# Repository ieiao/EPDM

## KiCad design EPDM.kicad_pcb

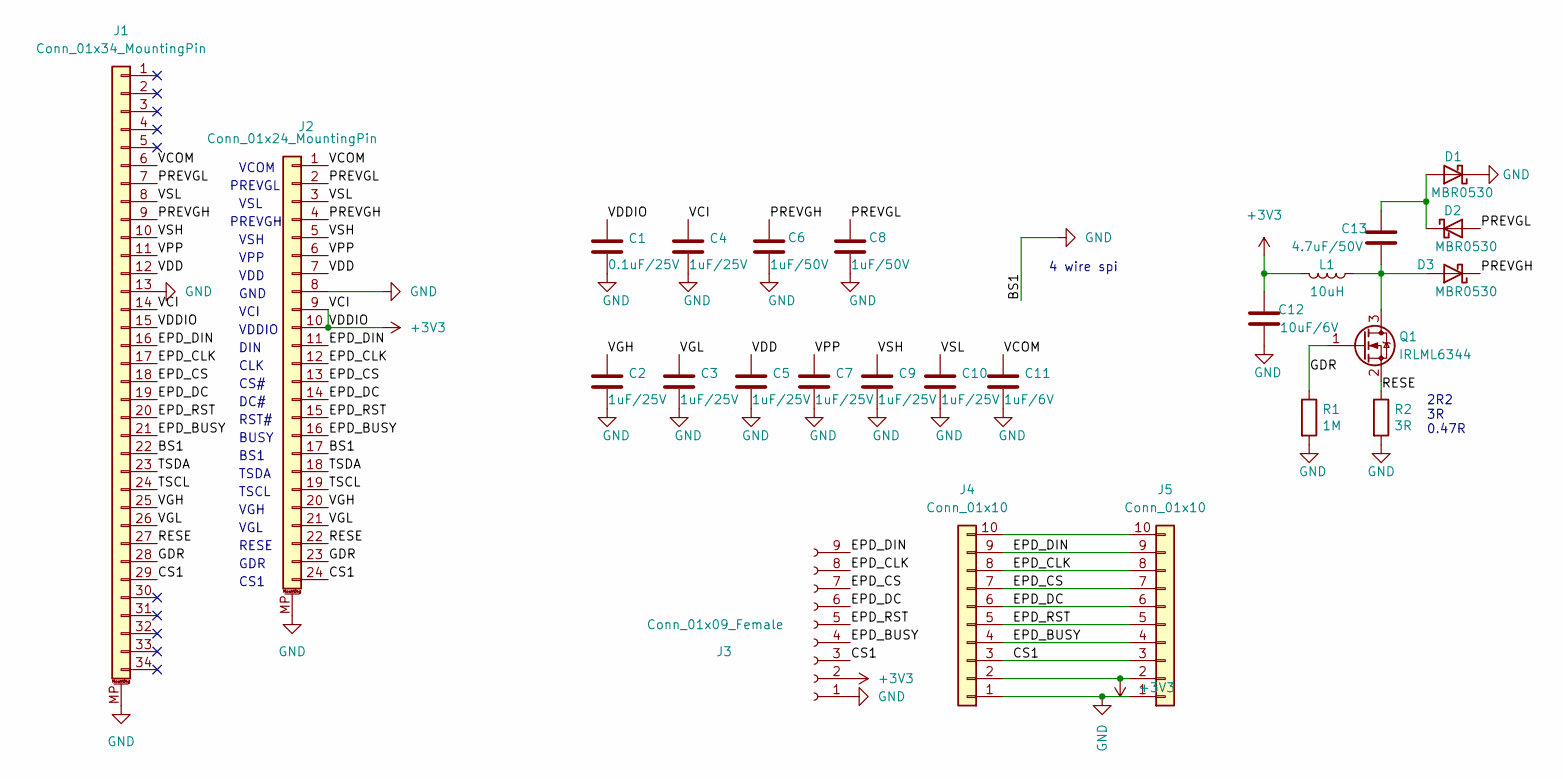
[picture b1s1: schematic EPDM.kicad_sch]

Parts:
C1: 0.1uF/25V; C_0603_1608Metric
C2, C3, C4, C5, C7, C9, C10: 1uF/25V; C_0603_1608Metric
C6, C8: 1uF/50V; C_0603_1608Metric
C11: 1uF/6V; C_0603_1608Metric
C12: 10uF/6V; C_0805_2012Metric
C13: 4.7uF/50V; C_0805_2012Metric
D1, D2, D3: MBR0530; D_SOD-123
J1: Conn_01x34_MountingPin; TE_3-1734839-4_1x34-1MP_P0.5mm_Horizontal
J2: Conn_01x24_MountingPin; TE_2-1734839-4_1x24-1MP_P0.5mm_Horizontal
J3: Conn_01x09_Female; PinHeader_1x09_P1.27mm_Vertical
J4: Conn_01x10; PinHeader_1x10_P1.27mm_Vertical
J5: Conn_01x10; PinHeader_1x10_P2.54mm_Vertical
L1: 10uH; L_Coilcraft_XxL4020
Q1: IRLML6344; SOT-23
R1: 1M; R_0603_1608Metric
R2: 3R; R_0603_1608Metric

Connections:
+3V3: C1.1, C4.1, C12.2, J1.14, J1.15, J2.9, J2.10, J3.2, J4.2, J5.2, L1.2
/CS1: J1.29, J2.24, J3.3, J4.3, J5.3
/EPD_BUSY: J1.21, J2.16, J3.4, J4.4, J5.4
/EPD_CLK: J1.17, J2.12, J3.8, J4.8, J5.8
/EPD_CS: J1.18, J2.13, J3.7, J4.7, J5.7
/EPD_DC: J1.19, J2.14, J3.6, J4.6, J5.6
/EPD_DIN: J1.16, J2.11, J3.9, J4.9, J5.9
/EPD_RST: J1.20, J2.15, J3.5, J4.5, J5.5
/GDR: J1.28, J2.23, Q1.1 (G), R1.1
/PREVGH: C6.1, D3.1 (K), J1.9, J2.4
/PREVGL: C8.1, D2.2 (A), J1.7, J2.2
/RESE: J1.27, J2.22, Q1.2 (S), R2.1
/TSCL: J1.24, J2.19
/TSDA: J1.23, J2.18
/VCOM: C11.1, J1.6, J2.1
/VDD: C5.1, J1.12, J2.7
/VGH: C2.1, J1.25, J2.20
/VGL: C3.1, J1.26, J2.21
/VPP: C7.1, J1.11, J2.6
/VSH: C9.1, J1.10, J2.5
/VSL: C10.1, J1.8, J2.3
GND: C1.2, C2.2, C3.2, C4.2, C5.2, C6.2, C7.2, C8.2, C9.2, C10.2, C11.2, C12.1, D1.1 (K), J1.13, J1.22, J1.MP (MountPin), J2.8, J2.17, J2.MP (MountPin), J3.1, J4.1, J5.1, R1.2, R2.2
unnamed: C13.1, D3.2 (A), L1.1, Q1.3 (D)
unnamed: C13.2, D1.2 (A), D2.1 (K)
unnamed: J4.10, J5.10

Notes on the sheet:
CS1
RST#
VDD
VPP
PREVGL
DC#
VGL
VDDIO
PREVGH
TSCL
DIN
VSL
VCI
VSH
VGH
CLK
4 wire spi
BS1
TSDA
2R2 3R 0.47R
RESE
GND
BUSY
GDR
CS#
VCOM

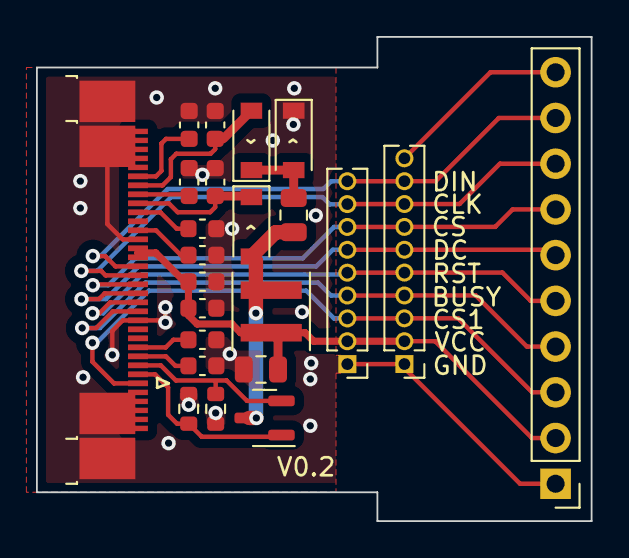
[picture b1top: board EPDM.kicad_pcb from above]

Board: 2 copper layers, 30.8 x 26.9 mm, 24 parts (0 on the bottom side), 25 nets.

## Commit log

2023-12-17 Init repository
2023-12-17 EPDM with adapter part
2023-12-17 EPDM without adapter part
2024-01-07 Set up 3D models
2024-11-28 Rotate some of components
2024-12-04 Size optimization
